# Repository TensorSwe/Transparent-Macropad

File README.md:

README.md
# Transparent Macropad

## About:
A 6-key macropad featuring a volume knob, an OLED screen, and 6 addressable LEDs.

**Project Link:**
https://stardance.hackclub.com/projects/45016

## Parts
* **MCU:** 1x Seeed Studio XIAO RP2040
* **Switches:** 6x MX-Style Switches
* **Keycaps:** 6x white blank DSA keycaps
* **Encoder:** 1x EC11 Rotary encoder with integrated push-button
* **Display:** 1x 0.91" SSD1306 I2C OLED (128x32)
* **Lighting:** 6x WS2812B LEDs
* **Other:** 6x through-hole 1N4148 Diodes, 4x M3x5mx4mm heatset inserts, 4x M3x10mm screws.

## Repository Layout
* `/cad`: 3D STEP assembly files for enclosure design
* `/firmware`: QMK firmware source code and keymap configuration
* `/pcb`: KiCad schematic, layout, and project files
* `/production`: Manufacturing outputs (Gerbers, STL 3D models, compiled `.uf2` firmware)

## Schematic, assembly & dimensions:

## Other Images:

_(The coding for the firmware was made using AI)_

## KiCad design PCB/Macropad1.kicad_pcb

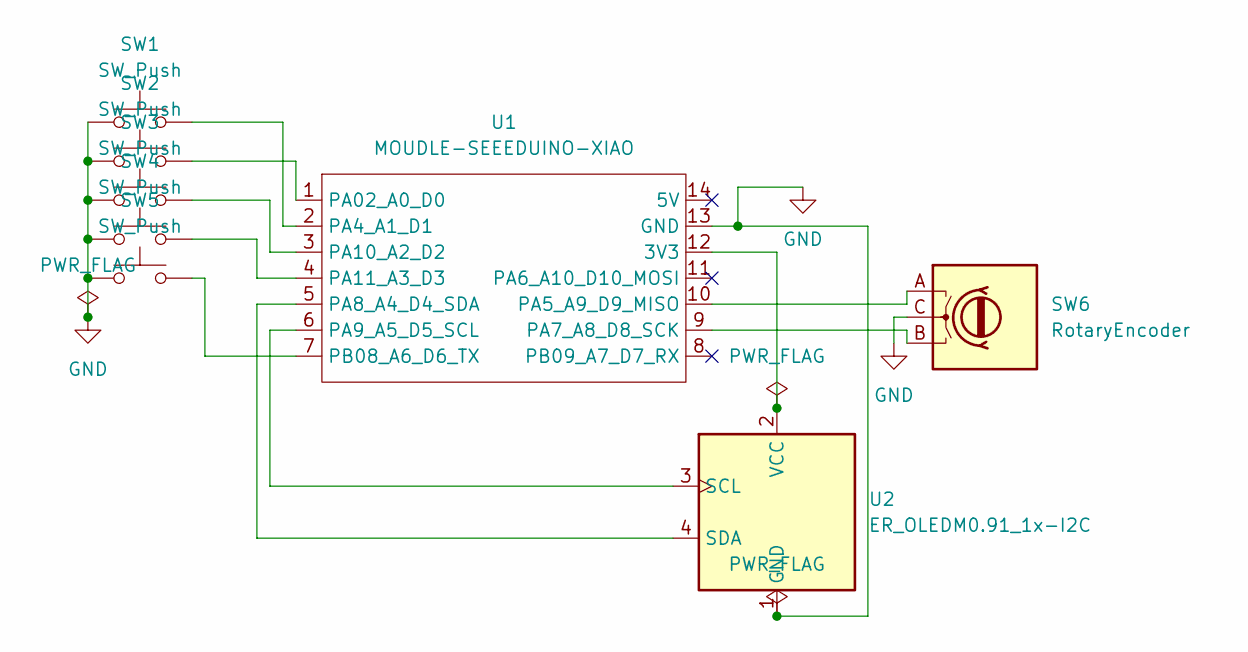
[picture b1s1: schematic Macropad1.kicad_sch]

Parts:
SW1, SW2, SW3, SW4, SW5: SW_Push; SW_Cherry_MX_1.00u_PCB
SW6: RotaryEncoder; RotaryEncoder_Alps_EC11E_Vertical_H20mm
U1: MOUDLE-SEEEDUINO-XIAO; XIAO-Generic-Hybrid-14P-2.54-21X17.8MM
U2: ER_OLEDM0.91_1x-I2C

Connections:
GND: SW1.1, SW2.1, SW3.1, SW4.1, SW5.1, SW6.C, U1.13 (GND), U2.1 (GND)
unnamed: U1.12 (3V3), U2.2 (VCC)
unnamed: SW2.2, U1.1 (PA02_A0_D0)
unnamed: SW1.2, U1.2 (PA4_A1_D1)
unnamed: SW6.A, U1.10 (PA5_A9_D9_MISO)
unnamed: SW6.B, U1.9 (PA7_A8_D8_SCK)
unnamed: U1.5 (PA8_A4_D4_SDA), U2.4 (SDA)
unnamed: U1.6 (PA9_A5_D5_SCL), U2.3 (SCL)
unnamed: SW3.2, U1.3 (PA10_A2_D2)
unnamed: SW4.2, U1.4 (PA11_A3_D3)
unnamed: SW5.2, U1.7 (PB08_A6_D6_TX)

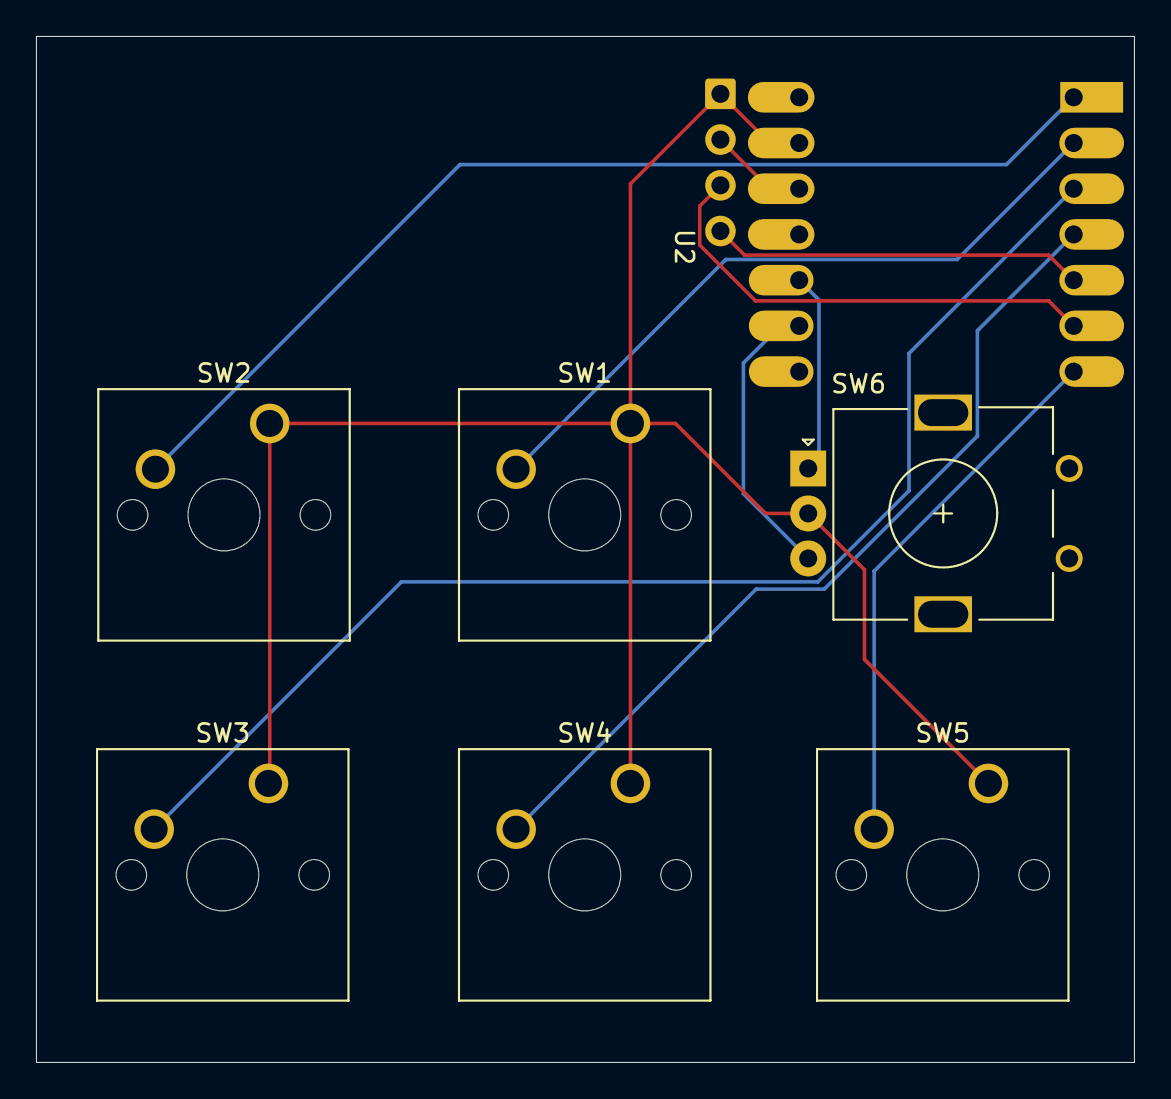
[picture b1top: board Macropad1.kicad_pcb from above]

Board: 2 copper layers, 61.0 x 57.0 mm, 8 parts (1 on the bottom side), 11 nets.
